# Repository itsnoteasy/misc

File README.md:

the io3360 zip is a through hole pcb and instructions designed in fritzing to convert the intellimouse optical 1.1 and wheel mouse optical to a pmw3360 by using the jkicklighter board on tindie and a teensy 2.0. It works fine as my daily driver although all it does is add weight. If you wanted to use the files a lighter approach would be to cut off the pcb in fritzing and add in wire holes, like how the ninox classic intellimouse is done on youtube.

The buttons folder is a cut off version of the smt pcb for those who want a light weight through hole build. There are pads for optional 1206 size pullups. I haven't tested it but it's probably ok, and you can order it from the cheaper pcb companies as it was completed in kicad, so has no errors.

the mouse8 folder is a work in progress similar project in kicad 6.0 nightly build using all surface mount parts, aiming for a lighter weight and lower cost. I uploaded the files so interested parties could submit bugfixes and comments. as of yet there are no successful builds, due to slow shipping times and tight budgets on my end. 

The gerbers are complete, the 3360 footprint is proprietary so I could not release it. it is freely available if hunted down though, as are the microswitch and ec10 footprints. 
if anyone cares to make a libre one I will add it here.

I moved the sensor forward for this build, only time will tell if that was the right decision. It is still possible to move it farther with a redesign, although I did not want to change it too much.

The pullup resistors are optional, a pair of 1206 size 10k is recommended for the wheel and a pair of 5k for each microswitch. I recommend not using an ultrabright led as it will exceed the safe average current limits of the mcu pin driving it. it is there merely as a power on indicator.

I am aware the schematic symbol pinout for the pmw3360 is in a different order to the chip, but the pins themselves are correct.

footprints are the property of their respective creators, can be sourced here:

https://www.overclock.net/forum/375-mice/1724838-progress-fully-custom-mouse-2.html#post27945424

https://www.overclock.net/forum/375-mice/1635281-new-ninox-mouse-ninox-astrum-swapable-shells-195.html#post27920712

mouse8onethree is an untested reworking of the mouse8 pcb to fit the ergo intellimouse1.3a shell, wmo and io1.1. It also adds a jumbled isp header. b1, b2, b3 are connected to a pair of through holes and can be jumpered over once the bootloader is programmed. 
ISP guide is here:

https://github.com/qmk/qmk_firmware/blob/master/docs/isp_flashing_guide.md

mouse is based on this post https://www.overclock.net/threads/reverse-engineering-3366.1561041/post-26323358

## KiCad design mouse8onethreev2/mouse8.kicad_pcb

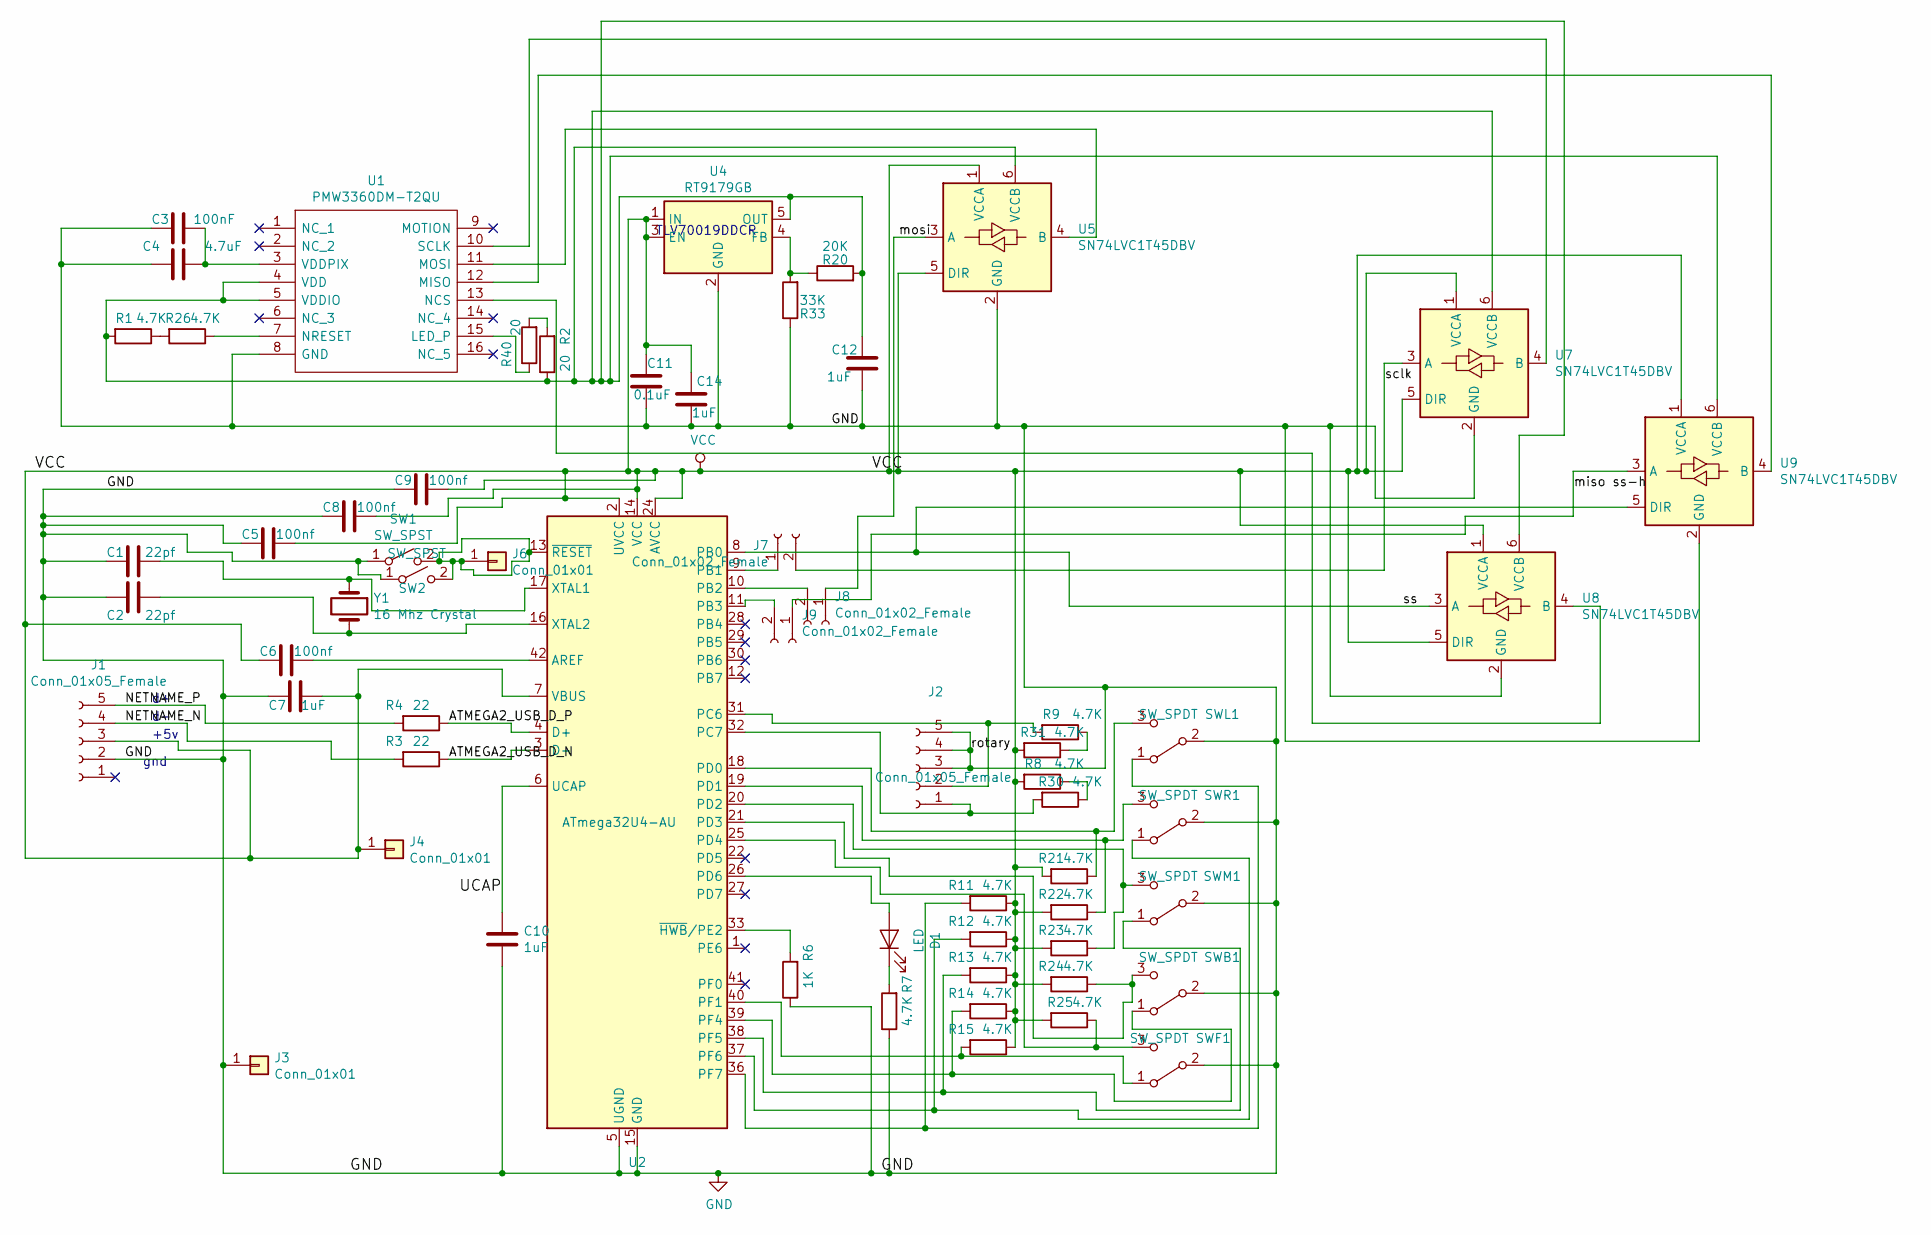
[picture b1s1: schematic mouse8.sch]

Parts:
C1, C2: 22pf; C_0805_2012Metric_Pad1.15x1.40mm_HandSolder
C3: 100nF; C_0805_2012Metric_Pad1.15x1.40mm_HandSolder
C4: 4.7uF; C_0805_2012Metric_Pad1.15x1.40mm_HandSolder
C5, C6, C8, C9: 100nf; C_0805_2012Metric_Pad1.15x1.40mm_HandSolder
C7, C10, C12, C14: 1uF; C_0805_2012Metric_Pad1.15x1.40mm_HandSolder
C11: 0.1uF; C_0805_2012Metric_Pad1.15x1.40mm_HandSolder
D1: LED; LED_D3.0mm
J1: Conn_01x05_Female; JST_PH_B5B-PH-K_1x05_P2.00mm_Vertical
J2: Conn_01x05_Female; ALPS_horzontal_encoder
J3, J4, J6: Conn_01x01; PinHeader_1x01_P2.54mm_Vertical
J7, J8, J9: Conn_01x02_Female; PinHeader_1x02_P2.54mm_Vertical
R1, R7, R8, R9, R11, R12, R13, R14, R15, R21, R22, R23, R24, R25, R26, R30, R31: 4.7K; R_0805_2012Metric_Pad1.15x1.40mm_HandSolder
R2, R40: 20; R_0805_2012Metric_Pad1.15x1.40mm_HandSolder
R3, R4: 22; R_0805_2012Metric_Pad1.15x1.40mm_HandSolder
R6: 1K; R_0805_2012Metric_Pad1.15x1.40mm_HandSolder
R20: 20K; R_0805_2012Metric_Pad1.15x1.40mm_HandSolder
R33: 33K; R_0805_2012Metric_Pad1.15x1.40mm_HandSolder
SW1, SW2: SW_SPST; SW_SPST_TL3342
SWB1: SW_SPDT; Microswitch_SPDT_D2F
SWF1: SW_SPDT; Microswitch_SPDT_D2F
SWL1: SW_SPDT; Microswitch_SPDT_D2F
SWM1: SW_SPDT; Microswitch_SPDT_D2F
SWR1: SW_SPDT; Microswitch_SPDT_D2F
U1: PMW3360DM-T2QU; PMW3360; Manufacturer_Part_Number PMW3360DM-T2QU
U2: ATmega32U4-AU; TQFP-44_10x10mm_P0.8mm
U4: RT9179GB; SOT-23-5
U5, U7, U8, U9: SN74LVC1T45DBV; SOT-23-6
Y1: 16 Mhz Crystal; Crystal_HC49-U_Vertical

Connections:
/ATMEGA2_USB_D_N: R3.1, U2.3 (D-)
/ATMEGA2_USB_D_P: R4.1, U2.4 (D+)
/NETNAME_N: J1.4, R3.2
/NETNAME_P: J1.5, R4.2
/UCAP: C10.1, U2.6 (UCAP)
/miso ss-h: J9.1, U9.3 (A)
/mosi: J8.1, U5.3 (A)
/sclk: J7.2, U7.3 (A)
/ss: U2.8 (PB0), U8.3 (A), U9.5 (DIR)
GND: C1.2, C2.2, C3.2, C4.2, C5.2, C7.2, C8.2, C9.2, C10.2, C11.2, C12.2, C14.2, J1.2, J2.3, J2.4, J2.5, J3.1, R6.1, R7.1, R33.1, SW1.1 (A), SW2.1 (A), SWB1.2 (B), SWF1.2 (B), SWL1.2 (B), SWM1.2 (B), SWR1.2 (B), U1.8 (GND), U2.5 (UGND), U2.15 (GND), U2.23 (GND), U2.35 (GND), U2.43 (GND), U4.2 (GND), U5.2 (GND), U7.2 (GND), U8.2 (GND), U9.2 (GND)
unnamed: C1.1, U2.17 (XTAL1), Y1.1
unnamed: C2.1, U2.16 (XTAL2), Y1.2
unnamed: C3.1, C4.1, U1.3 (VDDPIX)
unnamed: C6.1, U2.42 (AREF)
unnamed: C12.1, R1.2, R2.1, R20.2, U1.4 (VDD), U1.5 (VDDIO), U4.5 (OUT), U5.6 (VCCB), U7.6 (VCCB), U8.6 (VCCB), U9.6 (VCCB)
unnamed: D1.1 (K), R7.2
unnamed: D1.2 (A), U2.26 (PD6)
unnamed: J2.1, R30.2, U2.32 (PC7)
unnamed: J2.2, R9.2, U2.31 (PC6)
unnamed: J6.1, SW1.2 (B), SW2.2 (B), U2.13 (~RESET)
unnamed: J7.1, U2.9 (PB1)
unnamed: J8.2, U2.10 (PB2)
unnamed: J9.2, U2.11 (PB3)
unnamed: R1.1, R26.2
unnamed: R2.2, R40.2
unnamed: R6.2, U2.33 (~HWB~/PE2)
unnamed: R11.2, SWL1.1 (A), U2.36 (PF7)
unnamed: R12.2, SWR1.1 (A), U2.37 (PF6)
unnamed: R13.2, SWM1.1 (A), U2.38 (PF5)
unnamed: R14.2, SWB1.1 (A), U2.39 (PF4)
unnamed: R15.2, SWF1.1 (A), U2.40 (PF1)
unnamed: R20.1, R33.2, U4.4 (FB)
unnamed: R21.1, SWL1.3 (C), U2.18 (PD0)
unnamed: R22.1, SWR1.3 (C), U2.19 (PD1)
unnamed: R23.1, SWM1.3 (C), U2.20 (PD2)
unnamed: R24.1, SWB1.3 (C), U2.21 (PD3)
unnamed: R25.1, SWF1.3 (C), U2.25 (PD4)
unnamed: R26.1, U1.7 (NRESET)
unnamed: R8.1, R30.1
unnamed: R9.1, R31.1
unnamed: R40.1, U1.15 (LED_P)
unnamed: U1.10 (SCLK), U7.4 (B)
unnamed: U1.11 (MOSI), U5.4 (B)
unnamed: U1.12 (MISO), U9.4 (B)
unnamed: U1.13 (NCS), U8.4 (B)
VCC: C5.1, C6.2, C7.1, C8.1, C9.1, C11.1, C14.1, J1.3, J4.1, R8.2, R11.1, R12.1, R13.1, R14.1, R15.1, R21.2, R22.2, R23.2, R24.2, R25.2, R31.2, U2.2 (UVCC), U2.7 (VBUS), U2.14 (VCC), U2.24 (AVCC), U2.34 (VCC), U2.44 (AVCC), U4.1 (IN), U4.3 (EN), U5.1 (VCCA), U5.5 (DIR), U7.1 (VCCA), U7.5 (DIR), U8.1 (VCCA), U8.5 (DIR), U9.1 (VCCA)

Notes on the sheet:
TLV70019DDCR
gnd
+5v

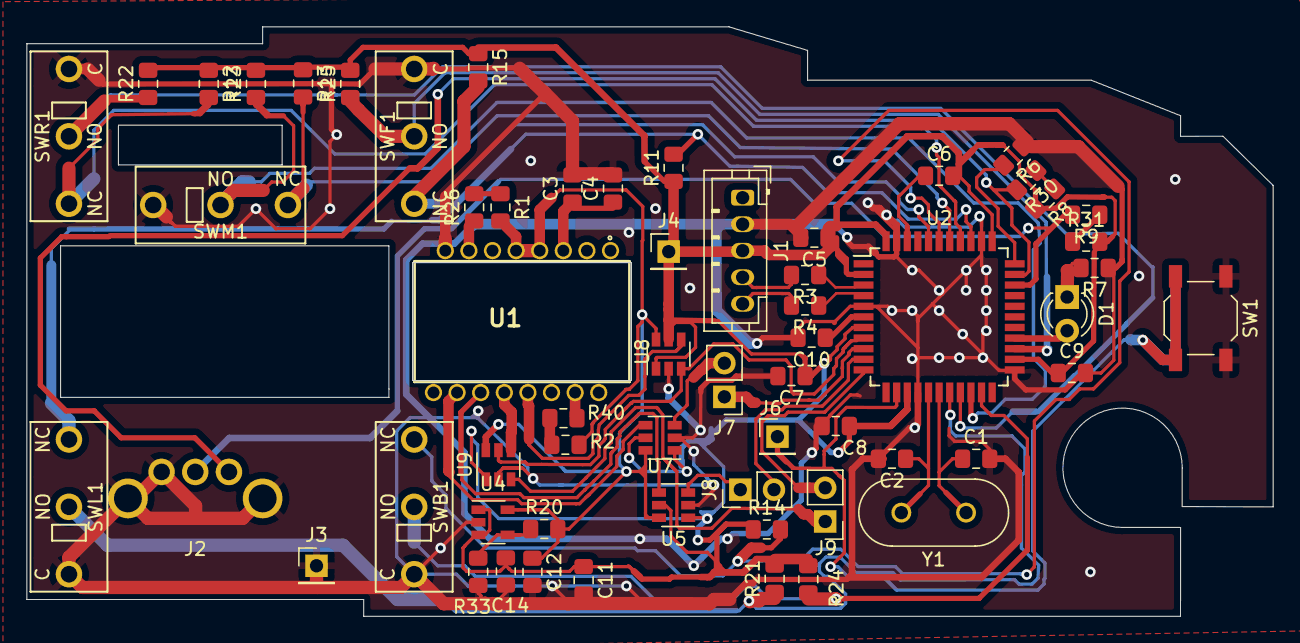
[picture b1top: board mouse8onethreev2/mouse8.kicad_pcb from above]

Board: 2 copper layers, 94.0 x 44.5 mm, 61 parts (1 on the bottom side), 46 nets.

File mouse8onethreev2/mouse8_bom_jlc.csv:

"Comment","Designator","Footprint","LCSC Part #"
"22pf","C2,C1","C_0805_2012Metric_Pad1.15x1.40mm_HandSolder","C1804"
"100nF","C3","C_0805_2012Metric_Pad1.15x1.40mm_HandSolder","C49678"
"4.7uF","C4","C_0805_2012Metric_Pad1.15x1.40mm_HandSolder","C1779"
"100nf","C9,C8,C5,C6","C_0805_2012Metric_Pad1.15x1.40mm_HandSolder","C49678"
"1uF","C10,C7,C12,C14","C_0805_2012Metric_Pad1.15x1.40mm_HandSolder","C28323"
"0.1uF","C11","C_0805_2012Metric_Pad1.15x1.40mm_HandSolder","C49678"
"20","R2,R40","R_0805_2012Metric_Pad1.15x1.40mm_HandSolder","C17544"
"22","R3,R4","R_0805_2012Metric_Pad1.15x1.40mm_HandSolder","C17561"
"1K","R6","R_0805_2012Metric_Pad1.15x1.40mm_HandSolder","C17673"
"4.7K","R11,R12,R13,R14,R15,R21,R22,R23,R24,R25,R8,R9,R1,R7,R26,R30,R31","R_0805_2012Metric_Pad1.15x1.40mm_HandSolder","C17673"
"20K","R20","R_0805_2012Metric_Pad1.15x1.40mm_HandSolder","C4328"
"33K","R33","R_0805_2012Metric_Pad1.15x1.40mm_HandSolder","C17633"
"ATmega32U4-AU","U2","TQFP-44_10x10mm_P0.8mm","C44854"
"RT9179GB","U4","SOT-23-5","C130831"
"SN74LVC1T45DBV","U5,U7,U8,U9","SOT-23-6","C7843"

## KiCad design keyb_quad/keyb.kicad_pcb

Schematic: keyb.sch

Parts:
D1, D2, D3, D4, D5: D; D_A-405_P7.62mm_Horizontal
J1, J2, J3, J4, J5: Conn_01x04_Female; MXOnly-1U
J1A1, J1B1, J2A1, J2B1, J3A1, J3B1, J4A1, J4B1, J5A1, J5B1: Conn_01x01_Female; PinSocket_1x01_P2.54mm_Vertical
JD1A1, JD1B1, JD2A1, JD2B1, JD3A1, JD3B1, JD4A1, JD4B1, JD5A1, JD5B1: Conn_01x01_Female; PinSocket_1x01_P2.54mm_Vertical
JG1A1, JG1B1, JG2A1, JG2B1, JG3A1, JG3B1, JG4A1, JG4B1, JG5A1, JG5B1: Conn_01x01_Female; PinSocket_1x01_P2.54mm_Vertical
JR1A1, JR1B1, JR2A1, JR2B1, JR3A1, JR3B1, JR4A1, JR4B1, JR5A1, JR5B1: Conn_01x01_Female; PinSocket_1x01_P2.54mm_Vertical
R1, R2, R3, R4, R5: R1K; R_Axial_DIN0207_L6.3mm_D2.5mm_P7.62mm_Horizontal

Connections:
/+5V: JR1A1.1, JR1B1.1, JR2A1.1, JR2B1.1, JR3A1.1, JR3B1.1, JR4A1.1, JR4B1.1, JR5A1.1, JR5B1.1, R1.2, R2.2, R3.2, R4.2, R5.2
/GND: J1.4, J2.4, J3.4, J4.4, J5.4, JG1A1.1, JG1B1.1, JG2A1.1, JG2B1.1, JG3A1.1, JG3B1.1, JG4A1.1, JG4B1.1, JG5A1.1, JG5B1.1
unnamed: D1.1 (K), JD1A1.1, JD1B1.1
unnamed: D1.2 (A), J1.2
unnamed: D2.1 (K), JD2A1.1, JD2B1.1
unnamed: D2.2 (A), J2.2
unnamed: D3.1 (K), JD3A1.1, JD3B1.1
unnamed: D3.2 (A), J3.2
unnamed: D4.1 (K), JD4A1.1, JD4B1.1
unnamed: D4.2 (A), J4.2
unnamed: D5.1 (K), JD5A1.1, JD5B1.1
unnamed: D5.2 (A), J5.2
unnamed: J1.1, J1A1.1, J1B1.1, J2.1, J2A1.1, J2B1.1, J3.1, J3A1.1, J3B1.1, J4.1, J4A1.1, J4B1.1, J5.1, J5A1.1, J5B1.1
unnamed: J1.3, R1.1
unnamed: J2.3, R2.1
unnamed: J3.3, R3.1
unnamed: J4.3, R4.1
unnamed: J5.3, R5.1

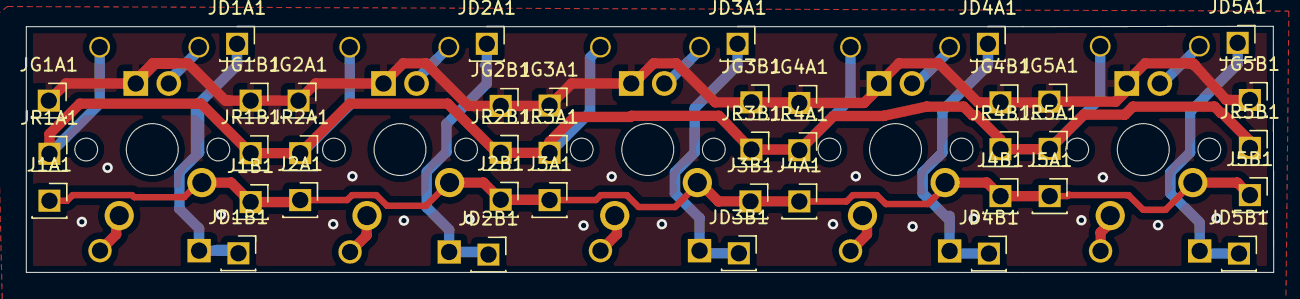
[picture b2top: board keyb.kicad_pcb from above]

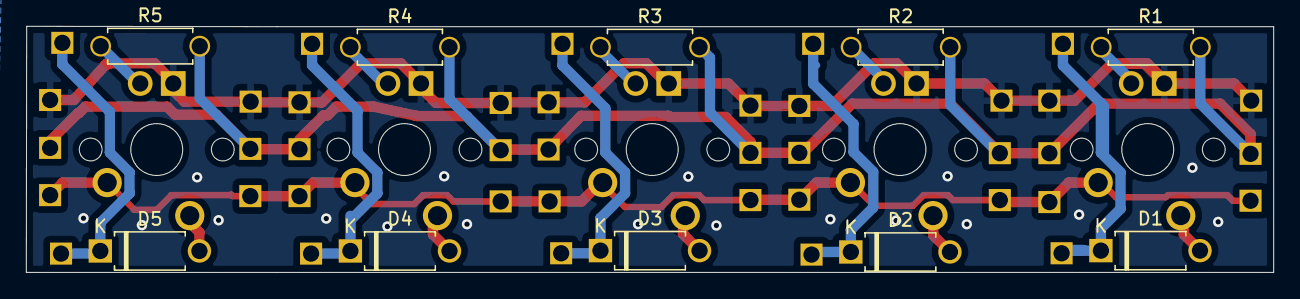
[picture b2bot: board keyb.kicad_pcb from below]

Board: 2 copper layers, 95.9 x 18.9 mm, 55 parts (10 on the bottom side), 18 nets.

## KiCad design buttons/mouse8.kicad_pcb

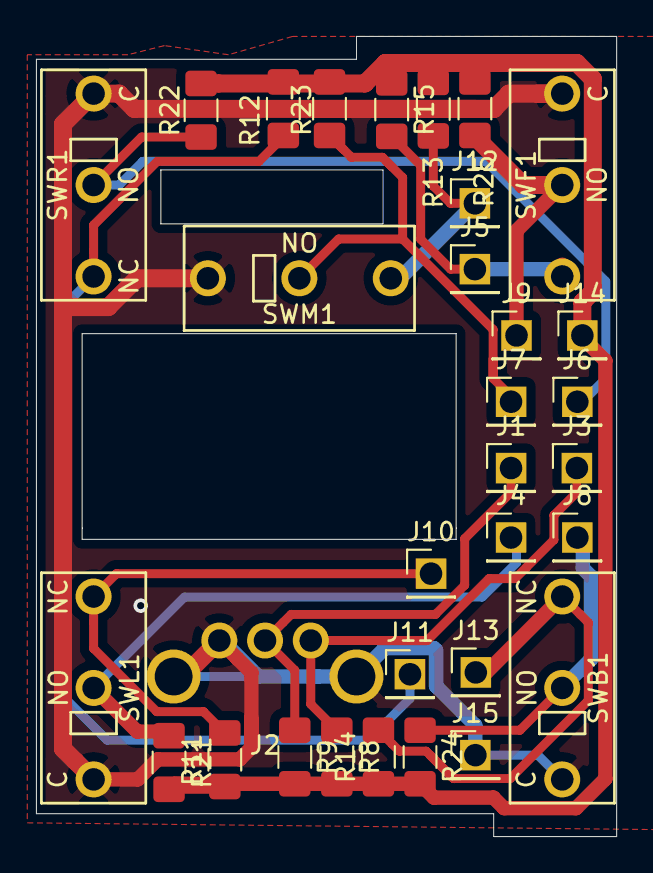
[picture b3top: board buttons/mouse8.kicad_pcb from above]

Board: 2 copper layers, 32.2 x 44.5 mm, 32 parts (0 on the bottom side), 14 nets.

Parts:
J1, J3, J4, J5, J6, J7, J8, J9, J10, J11, J12, J13, J14, J15: Conn_01x01; PinHeader_1x01_P2.54mm_Vertical
J2: Conn_01x05_Female; ALPS_horzontal_encoder
R8, R9: 10K; R_1206_3216Metric_Pad1.42x1.75mm_HandSolder
R11, R12, R13, R14, R15, R21, R22, R23, R24, R25: 5K; R_1206_3216Metric_Pad1.42x1.75mm_HandSolder
SWB1: SW_SPDT; Microswitch_SPDT_D2F
SWF1: SW_SPDT; Microswitch_SPDT_D2F
SWL1: SW_SPDT; Microswitch_SPDT_D2F
SWM1: SW_SPDT; Microswitch_SPDT_D2F
SWR1: SW_SPDT; Microswitch_SPDT_D2F

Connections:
GND: J2.3, J2.4, J2.5, J15.1, SWB1.2, SWF1.2, SWL1.2, SWM1.2, SWR1.2
unnamed: J1.1, J2.2, R9.1
unnamed: J2.1, J3.1, R8.1
unnamed: J4.1, R21.1, SWL1.3
unnamed: J5.1, R15.2, SWF1.1
unnamed: J6.1, R22.1, SWR1.3
unnamed: J7.1, R23.1, SWM1.3
unnamed: J8.1, R24.1, SWB1.3
unnamed: J9.1, R25.1, SWF1.3
unnamed: J10.1, R11.2, SWL1.1
unnamed: J11.1, R12.2, SWR1.1
unnamed: J12.1, R13.2, SWM1.1
unnamed: J13.1, R14.2, SWB1.1
unnamed: J14.1, R8.2, R9.2, R11.1, R12.1, R13.1, R14.1, R15.1, R21.2, R22.2, R23.2, R24.2, R25.2

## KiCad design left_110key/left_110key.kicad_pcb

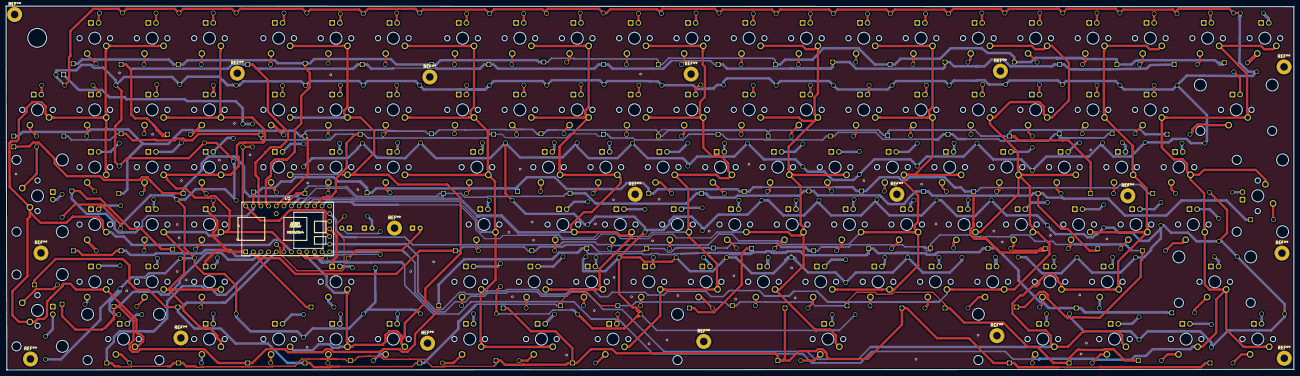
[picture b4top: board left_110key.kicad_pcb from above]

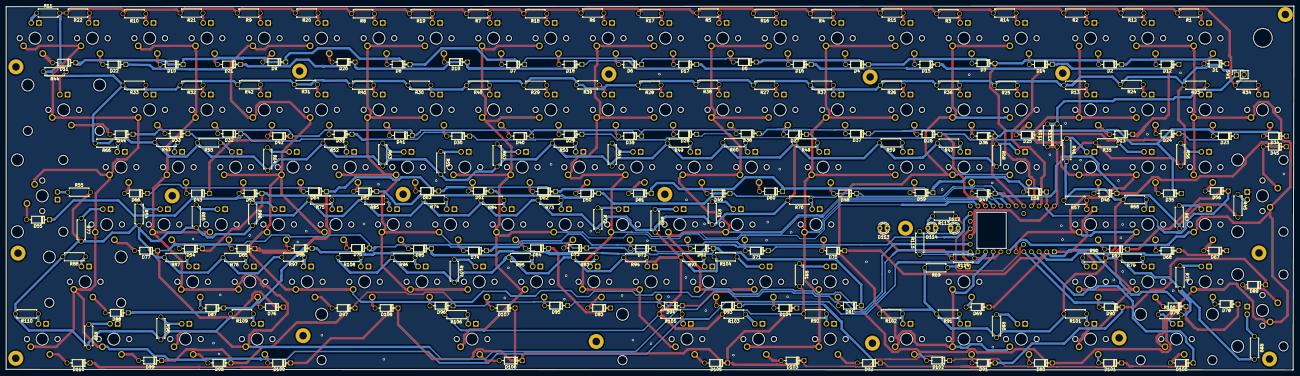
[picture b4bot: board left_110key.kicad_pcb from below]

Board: 2 copper layers, 428.1 x 121.0 mm, 340 parts (229 on the bottom side), 251 nets.

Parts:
D1, D2, D3, D4, D5, D6, D7, D8, D9, D10, D11, D12, D13, D14, D15, D16, D17, D18, D19, D20, D21, D22, D23, D24, D25, D26, D27, D28, D29, D30, D31, D32, D33, D34, D35, D36, D37, D38, D39, D40, D41, D42, D43, D44, D45, D46, D47, D48, D49, D50, D51, D52, D53, D54, D55, D56, D57, D58, D59, D60, D61, D62, D63, D64, D65, D66, D67, D68, D69, D70, D71, D72, D73, D74, D75, D76, D77, D78, D79, D80, D81, D82, D83, D84, D85, D86, D87, D88, D89, D90, D91, D92, D93, D94, D95, D96, D97, D98, D99, D100, D101, D102, D103, D104, D105, D106, D107, D108, D109, D110: D; D_DO-35_SOD27_P7.62mm_Horizontal
D112, D113, D114: LED; LED_D3.0mm
J1, J2, J3, J4, J5, J6, J7, J8, J9, J10, J11, J12, J13, J14, J15, J16, J17, J18, J19, J20, J21, J22, J23, J24, J25, J26, J27, J28, J29, J30, J31, J32, J33, J34, J35, J36, J37, J38, J39, J40, J41, J42, J43, J46, J47, J49, J50, J51, J52, J53, J54, J56, J57, J58, J59, J60, J61, J62, J63, J64, J65, J66, J67, J68, J69, J71, J72, J73, J74, J75, J76, J77, J78, J79, J80, J82, J83, J84, J85, J86, J87, J90, J91, J93, J94, J95, J96, J97, J101, J102, J104, J107, J108: Conn_01x04_Male; MXOnly-1U
J44, J45, J89, J100: Conn_01x04_Male; MXOnly-2U
J48: Conn_01x04_Male; MXOnly-1.5U
J55: Conn_01x04_Male; MXOnly-ISO-ROTATED
J70: Conn_01x04_Male; MXOnly-1.75U
J81, J92, J98, J99, J103, J105, J109, J110: Conn_01x04_Male; MXOnly-1.25U
J88: Conn_01x04_Male; MXOnly-2.75U
J106: Conn_01x04_Male; MXOnly-6.25U
R1, R2, R3, R4, R5, R6, R7, R8, R9, R10, R11, R12, R13, R14, R15, R16, R17, R18, R19, R20, R21, R22, R23, R24, R25, R26, R27, R28, R29, R30, R31, R32, R33, R34, R35, R36, R37, R38, R39, R40, R41, R42, R43, R44, R45, R46, R47, R48, R49, R50, R51, R52, R53, R54, R55, R56, R57, R58, R59, R60, R61, R62, R63, R64, R65, R66, R67, R68, R69, R70, R71, R72, R73, R74, R75, R76, R77, R78, R79, R80, R81, R82, R83, R84, R85, R86, R87, R88, R89, R90, R91, R92, R93, R94, R95, R96, R97, R98, R99, R100, R101, R102, R103, R104, R105, R106, R107, R108, R109, R110, R111, R112, R113, R114, R115: R; R_Axial_DIN0207_L6.3mm_D2.5mm_P7.62mm_Horizontal
SW1: SW_SPST; PinSocket_1x02_P2.54mm_Vertical
U1: TEENSY2.0; Teensy2.0

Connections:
COL0: J1.1, J12.1, J23.1, J34.1, J45.1, J56.1, J67.1, J78.1, J89.1, J100.1, U1.7
COL1: J2.1, J13.1, J24.1, J35.1, J46.1, J57.1, J68.1, J79.1, J90.1, J101.1, U1.6
COL2: J3.1, J14.1, J25.1, J36.1, J47.1, J58.1, J69.1, J80.1, J91.1, J102.1, U1.9
COL3: J4.1, J15.1, J26.1, J37.1, J48.1, J59.1, J70.1, J81.1, J92.1, J103.1, U1.21
COL4: J5.1, J16.1, J27.1, J38.1, J49.1, J60.1, J71.1, J82.1, J93.1, J104.1, U1.23
COL5: J6.1, J17.1, J28.1, J39.1, J50.1, J61.1, J72.1, J83.1, J94.1, J105.1, U1.22
COL6: J7.1, J18.1, J29.1, J40.1, J51.1, J62.1, J73.1, J84.1, J95.1, J106.1, U1.19
COL7: J8.1, J19.1, J30.1, J41.1, J52.1, J63.1, J74.1, J85.1, J96.1, J107.1, U1.17
COL8: J9.1, J20.1, J31.1, J42.1, J53.1, J64.1, J75.1, J86.1, J97.1, J108.1, U1.13
COL9: J10.1, J21.1, J32.1, J43.1, J54.1, J65.1, J76.1, J87.1, J98.1, J109.1, U1.12
COL10: J11.1, J22.1, J33.1, J44.1, J55.1, J66.1, J77.1, J88.1, J99.1, J110.1, U1.10
GND: D112.1, D113.1, D114.1, J1.4, J2.4, J3.4, J4.4, J5.4, J6.4, J7.4, J8.4, J9.4, J10.4, J11.4, J12.4, J13.4, J14.4, J15.4, J16.4, J17.4, J18.4, J19.4, J20.4, J21.4, J22.4, J23.4, J24.4, J25.4, J26.4, J27.4, J28.4, J29.4, J30.4, J31.4, J32.4, J33.4, J34.4, J35.4, J36.4, J37.4, J38.4, J39.4, J40.4, J41.4, J42.4, J43.4, J44.4, J45.4, J46.4, J47.4, J48.4, J49.4, J50.4, J51.4, J52.4, J53.4, J54.4, J55.4, J56.4, J57.4, J58.4, J59.4, J60.4, J61.4, J62.4, J63.4, J64.4, J65.4, J66.4, J67.4, J68.4, J69.4, J70.4, J71.4, J72.4, J73.4, J74.4, J75.4, J76.4, J77.4, J78.4, J79.4, J80.4, J81.4, J82.4, J83.4, J84.4, J85.4, J86.4, J87.4, J88.4, J89.4, J90.4, J91.4, J92.4, J93.4, J94.4, J95.4, J96.4, J97.4, J98.4, J99.4, J100.4, J101.4, J102.4, J103.4, J104.4, J105.4, J106.4, J107.4, J108.4, J109.4, J110.4, U1.1, U1.15
unnamed: D1.2, J1.2
unnamed: D2.2, J2.2
unnamed: D3.2, J3.2
unnamed: D4.2, J4.2
unnamed: D5.2, J5.2
unnamed: D6.2, J6.2
unnamed: D7.2, J7.2
unnamed: D8.2, J8.2
unnamed: D9.2, J9.2
unnamed: D10.2, J10.2
unnamed: D11.2, J11.2
unnamed: D12.2, J12.2
unnamed: D13.2, J13.2
unnamed: D14.2, J14.2
unnamed: D15.2, J15.2
unnamed: D16.2, J16.2
unnamed: D17.2, J17.2
unnamed: D18.2, J18.2
unnamed: D19.2, J19.2
unnamed: D20.2, J20.2
unnamed: D21.2, J21.2
unnamed: D22.2, J22.2
unnamed: D23.2, J23.2
unnamed: D24.2, J24.2
unnamed: D25.2, J25.2
unnamed: D26.2, J26.2
unnamed: D27.2, J27.2
unnamed: D28.2, J28.2
unnamed: D29.2, J29.2
unnamed: D30.2, J30.2
unnamed: D31.2, J31.2
unnamed: D32.2, J32.2
unnamed: D33.2, J33.2
unnamed: D34.2, J34.2
unnamed: D35.2, J35.2
unnamed: D36.2, J36.2
unnamed: D37.2, J37.2
unnamed: D38.2, J38.2
unnamed: D39.2, J39.2
unnamed: D40.2, J40.2
unnamed: D41.2, J41.2
unnamed: D42.2, J42.2
unnamed: D43.2, J43.2
unnamed: D44.2, J44.2
unnamed: D45.2, J45.2
unnamed: D46.2, J46.2
unnamed: D47.2, J47.2
unnamed: D48.2, J48.2
unnamed: D49.2, J49.2
unnamed: D50.2, J50.2
unnamed: D51.2, J51.2
unnamed: D52.2, J52.2
unnamed: D53.2, J53.2
unnamed: D54.2, J54.2
unnamed: D55.2, J55.2
unnamed: D56.2, J56.2
unnamed: D57.2, J57.2
unnamed: D58.2, J58.2
unnamed: D59.2, J59.2
unnamed: D60.2, J60.2
unnamed: D61.2, J61.2
unnamed: D62.2, J62.2
unnamed: D63.2, J63.2
unnamed: D64.2, J64.2
unnamed: D65.2, J65.2
unnamed: D66.2, J66.2
unnamed: D67.2, J67.2
unnamed: D68.2, J68.2
unnamed: D69.2, J69.2
unnamed: D70.2, J70.2
unnamed: D71.2, J71.2
unnamed: D72.2, J72.2
unnamed: D73.2, J73.2
unnamed: D74.2, J74.2
unnamed: D75.2, J75.2
unnamed: D76.2, J76.2
unnamed: D77.2, J77.2
unnamed: D78.2, J78.2
unnamed: D79.2, J79.2
unnamed: D80.2, J80.2
unnamed: D81.2, J81.2
unnamed: D82.2, J82.2
unnamed: D83.2, J83.2
unnamed: D84.2, J84.2
unnamed: D85.2, J85.2
unnamed: D86.2, J86.2
unnamed: D87.2, J87.2
unnamed: D88.2, J88.2
unnamed: D89.2, J89.2
unnamed: D90.2, J90.2
unnamed: D91.2, J91.2
unnamed: D92.2, J92.2
unnamed: D93.2, J93.2
unnamed: D94.2, J94.2
unnamed: D95.2, J95.2
unnamed: D96.2, J96.2
unnamed: D97.2, J97.2
unnamed: D98.2, J98.2
unnamed: D99.2, J99.2
unnamed: D100.2, J100.2
unnamed: D101.2, J101.2
unnamed: D102.2, J102.2
unnamed: D103.2, J103.2
unnamed: D104.2, J104.2
unnamed: D105.2, J105.2
unnamed: D106.2, J106.2
unnamed: D107.2, J107.2
unnamed: D108.2, J108.2
unnamed: D109.2, J109.2
unnamed: D110.2, J110.2
unnamed: D112.2, R115.2
unnamed: D113.2, R114.2
unnamed: D114.2, R113.2
unnamed: J1.3, R1.1
unnamed: J2.3, R2.1
unnamed: J3.3, R3.1
unnamed: J4.3, R4.1
unnamed: J5.3, R5.1
unnamed: J6.3, R6.1
unnamed: J7.3, R7.1
unnamed: J8.3, R8.1
unnamed: J9.3, R9.1
unnamed: J10.3, R10.1
unnamed: J11.3, R11.1
unnamed: J12.3, R12.1
unnamed: J13.3, R13.1
unnamed: J14.3, R14.1
unnamed: J15.3, R15.1
unnamed: J16.3, R16.1
unnamed: J17.3, R17.1
unnamed: J18.3, R18.1
unnamed: J19.3, R19.1
unnamed: J20.3, R20.1
unnamed: J21.3, R21.1
unnamed: J22.3, R22.1
unnamed: J23.3, R23.1
unnamed: J24.3, R24.1
unnamed: J25.3, R25.1
unnamed: J26.3, R26.1
unnamed: J27.3, R27.1
unnamed: J28.3, R28.1
unnamed: J29.3, R29.1
unnamed: J30.3, R30.1
unnamed: J31.3, R31.1
unnamed: J32.3, R32.1
unnamed: J33.3, R33.1
unnamed: J34.3, R34.1
unnamed: J35.3, R35.1
unnamed: J36.3, R36.1
unnamed: J37.3, R37.1
unnamed: J38.3, R38.1
unnamed: J39.3, R39.1
unnamed: J40.3, R40.1
unnamed: J41.3, R41.1
unnamed: J42.3, R42.1
unnamed: J43.3, R43.1
unnamed: J44.3, R44.1
unnamed: J45.3, R45.1
unnamed: J46.3, R46.1
unnamed: J47.3, R47.1
unnamed: J48.3, R48.1
unnamed: J49.3, R49.1
unnamed: J50.3, R50.1
unnamed: J51.3, R51.1
unnamed: J52.3, R52.1
unnamed: J53.3, R53.1
unnamed: J54.3, R54.1
unnamed: J55.3, R55.1
unnamed: J56.3, R56.1
unnamed: J57.3, R57.1
unnamed: J58.3, R58.1
unnamed: J59.3, R59.1
unnamed: J60.3, R60.1
unnamed: J61.3, R61.1
unnamed: J62.3, R62.1
unnamed: J63.3, R63.1
unnamed: J64.3, R64.1
unnamed: J65.3, R65.1
unnamed: J66.3, R66.1
unnamed: J67.3, R67.1
unnamed: J68.3, R68.1
unnamed: J69.3, R69.1
unnamed: J70.3, R70.1
unnamed: J71.3, R71.1
unnamed: J72.3, R72.1
unnamed: J73.3, R73.1
unnamed: J74.3, R74.1
unnamed: J75.3, R75.1
unnamed: J76.3, R76.1
unnamed: J77.3, R77.1
unnamed: J78.3, R78.1
unnamed: J79.3, R79.1
unnamed: J80.3, R80.1
unnamed: J81.3, R81.1
unnamed: J82.3, R82.1
unnamed: J83.3, R83.1
unnamed: J84.3, R84.1
unnamed: J85.3, R85.1
unnamed: J86.3, R86.1
unnamed: J87.3, R87.1
unnamed: J88.3, R88.1
unnamed: J89.3, R89.1
unnamed: J90.3, R90.1
unnamed: J91.3, R91.1
unnamed: J92.3, R92.1
unnamed: J93.3, R93.1
unnamed: J94.3, R94.1
unnamed: J95.3, R95.1
unnamed: J96.3, R96.1
unnamed: J97.3, R97.1
unnamed: J98.3, R98.1
unnamed: J99.3, R99.1
unnamed: J100.3, R100.1
unnamed: J101.3, R101.1
unnamed: J102.3, R102.1
unnamed: J103.3, R103.1
unnamed: J104.3, R104.1
unnamed: J105.3, R105.1
unnamed: J106.3, R106.1
unnamed: J107.3, R107.1
unnamed: J108.3, R108.1
unnamed: J109.3, R109.1
unnamed: J110.3, R110.1
unnamed: R1.2, R2.2, R3.2, R4.2, R5.2, R6.2, R7.2, R8.2, R9.2, R10.2, R11.2, R12.2, R13.2, R14.2, R15.2, R16.2, R17.2, R18.2, R19.2, R20.2, R21.2, R22.2, R23.2, R24.2, R25.2, R26.2, R27.2, R28.2, R29.2, R30.2, R31.2, R32.2, R33.2, R34.2, R35.2, R36.2, R37.2, R38.2, R39.2, R40.2, R41.2, R42.2, R43.2, R44.2, R45.2, R46.2, R47.2, R48.2, R49.2, R50.2, R51.2, R52.2, R53.2, R54.2, R55.2, R56.2, R57.2, R58.2, R59.2, R60.2, R61.2, R62.2, R63.2, R64.2, R65.2, R66.2, R67.2, R68.2, R69.2, R70.2, R71.2, R72.2, R73.2, R74.2, R75.2, R76.2, R77.2, R78.2, R79.2, R80.2, R81.2, R82.2, R83.2, R84.2, R85.2, R86.2, R87.2, R88.2, R89.2, R90.2, R91.2, R92.2, R93.2, R94.2, R95.2, R96.2, R97.2, R98.2, R99.2, R100.2, R101.2, R102.2, R103.2, R104.2, R105.2, R106.2, R107.2, R108.2, R109.2, R110.2, SW1.2
unnamed: R111.1, R112.1, U1.14, U1.29
unnamed: R111.2, R112.2, SW1.1
unnamed: R113.1, U1.31
unnamed: R114.1, U1.8
unnamed: R115.1, U1.11
ROW0: D1.1, D2.1, D3.1, D4.1, D5.1, D6.1, D7.1, D8.1, D9.1, D10.1, D11.1, U1.26
ROW1: D12.1, D13.1, D14.1, D15.1, D16.1, D17.1, D18.1, D19.1, D20.1, D21.1, D22.1, U1.27
ROW2: D23.1, D24.1, D25.1, D26.1, D27.1, D28.1, D29.1, D30.1, D31.1, D32.1, D33.1, U1.20
ROW3: D34.1, D35.1, D36.1, D37.1, D38.1, D39.1, D40.1, D41.1, D42.1, D43.1, D44.1, U1.25
ROW4: D45.1, D46.1, D47.1, D48.1, D49.1, D50.1, D51.1, D52.1, D53.1, D54.1, D55.1, U1.24
ROW5: D56.1, D57.1, D58.1, D59.1, D60.1, D61.1, D62.1, D63.1, D64.1, D65.1, D66.1, U1.28
ROW6: D67.1, D68.1, D69.1, D70.1, D71.1, D72.1, D73.1, D74.1, D75.1, D76.1, D77.1, U1.2
ROW7: D78.1, D79.1, D80.1, D81.1, D82.1, D83.1, D84.1, D85.1, D86.1, D87.1, D88.1, U1.3
ROW8: D89.1, D90.1, D91.1, D92.1, D93.1, D94.1, D95.1, D96.1, D97.1, D98.1, D99.1, U1.5
ROW9: D100.1, D101.1, D102.1, D103.1, D104.1, D105.1, D106.1, D107.1, D108.1, D109.1, D110.1, U1.4

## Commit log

2020-11-03 Add files via upload
    19.00mm spacing handwired 5x4 for a low cost preonic plate
2026-04-03 Add files via upload
    a collection of automotive ideas from various forums
